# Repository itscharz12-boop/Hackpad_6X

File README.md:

# Hackpad 6x

Hackpad 6x is a small but very over-engineered macropad that I designed because apparently a normal keyboard was not enough :)

The idea was to make a compact control pad that could do a bit of everything: media controls, shortcuts, gaming controls, numpad functions, and displaying useless (but cool) information from my PC.

Basically, I wanted an "infinite keys" macropad where a few buttons could become a lot of buttons through layers.

(yes, this did start as "I'll just make a simple macropad" and then somehow became OLEDs, RGB, and a PC monitoring system. I have no idea how this happened.)

Images of this hackpad can be found in the "images" folder.

Showcase Video (For Hack Club's Stardance event) also available at this link:
https://drive.google.com/file/d/1zJtfslaftjd1Jd6tR7nyllq0msRzVyGn/view?usp=sharing

---

# Features

- 5 different profiles/layers
- Rotary encoder with push button
- OLED display
- RGB lighting
- PC telemetry

The PC telemetry shows:
- CPU usage
- GPU usage
- Volume
- Brightness
(Useful for checking your PC performance without moving your eyes approximately 20cm up to look at your monitor.)

---

# Hardware

The hackpad is built around a Seeed XIAO RP2040.

Parts:

- Seeed XIAO RP2040
- 8x Cherry MX switches
- 8x keycaps
- EC11 rotary encoder
- OLED display
- 16x RGB LEDs
- Custom PCB
- 3D printed case

---

# Assembly

### PCB Assembly

Solder all components onto the PCB:

- Diodes
- RGB LEDs
- OLED
- Rotary encoder
- XIAO RP2040

Please please please check the orientation twice, you won't regret it

### Case Assembly

- Install heat-set inserts
- put the top plate on the bottom 

### Firmware

Hackpad 6x uses QMK firmware.

The firmware includes:

- Layer switching
- Encoder controls
- RGB effects
- OLED graphics
- RAW HID PC communication
  and many more features shown in the video (heres the link again, u should rly watch it: https://drive.google.com/file/d/1zJtfslaftjd1Jd6tR7nyllq0msRzVyGn/view?usp=sharing)

---

### Hackpad DataLink

HackpadDataLink is a Python script that sends PC information to the hackpad.

Currently supported:

- CPU usage
- GPU usage
- Volume
- Brightness

---

# Images

### AI Usage

AI was used minimally throughout this project. The only instance of AI use was fixing compile errors in the firmware. This was done with VS code's built in AI, not quite sure what its called. Aside from this, no other AI tools were used in the making of this project.

Hackpad 6x was built as a personal project to learn PCB design, CAD, QMK firmware, and hardware/software integration. I think this might be the single most electronically complex thing I have ever made.

Huge thanks to Hack Club for making this program possible :)

(Also thanks to Google, Stack Overflow, and whoever wrote the forum post that fixed my kicad)

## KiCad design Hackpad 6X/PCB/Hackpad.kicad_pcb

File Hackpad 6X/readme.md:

# Hackpad 6x

Hackpad 6x is a multi-profile macropad designed to act as an all-purpose desktop control pad. Instead of relying on a large number of physical keys, it uses multiple profiles, a rotary encoder, an OLED display, RGB lighting, and PC telemetry to turn a compact set of inputs into a flexible control surface for media, desktop shortcuts, gaming, and numpad functions.

The goal of this project was to create an “infinite keys” style macropad: a device where a small number of physical inputs can perform a much larger range of tasks through layers.

Hackpad 6x was designed as an omnipurpose desktop macropad rather than a single-purpose keypad. The focus of the project was flexibility: combining multiple profiles, a rotary encoder, OLED feedback, RGB lighting, and PC-side telemetry to make a compact but highly adaptable control device.

---
## Quick Start

1. **Build the hardware** — Assemble the macropad using the PCB, case, switches, and other components listed in the BOM
2. **Flash the firmware** — Install QMK and flash the firmware to the Seeed XIAO RP2040
3. **Install software** — Set up the HackpadDataLink Python script on your PC
4. **Configure profiles** — Customize keybinds and OLED graphics as needed

---

## Features

- Multi-profile layout system for different use cases
- Rotary encoder with push button for quick control input
- OLED display with profile-specific graphics and live system information
- RGB lighting effects with multiple selectable modes
- Media and desktop shortcut controls
- Dual numpad layers for keybinds in games or editors when using 60, 65, 70% keyboards etc.
- Gaming profile for commonly used controls
- PC telemetry support displaying:
  - CPU usage
  - GPU usage
  - System volume
  - Display brightness

---

## Profiles

Hackpad 6x uses 5 profiles:

- Layer 0 — Home / Base
- Layer 1 — Media / Screen Control
- Layer 2 — Numpad A
- Layer 3 — Numpad B
- Layer 4 — Gaming

---

## Hardware

Hackpad 6x is built around a Seeed XIAO RP2040 and includes:

- 8 Cherry MX switches
- 8 keycaps
- 1 rotary encoder with push button
- 1 0.91" OLED display
- 18 RGB LEDs
- 9 diodes
- 6 M3 screws
- 6 M3 heat-set inserts
- Custom 2-layer PCB
- 3D printed case

---

## Bill of Materials (BOM)

| Part                                 | Quantity |
| ------------------------------------ | -------: | 
| Seeed XIAO RP2040                    |        1 | 
| Cherry MX switches                   |        8 |
| Keycaps                              |        8 |
| EC11 rotary encoder with push button |        1 |
| 0.91" OLED display                   |        1 | 
| RGB LEDs                             |       18 |
| Diodes                               |        9 |
| Custom PCB                           |        1 | 
| 3D printed case (BASE + TOP)         |        1 | 
| M3 screws                            |        6 | 
| M3 heatset inserts                   |        6 | 
| Encoder knob                         |        1 | 

---

## Setup & Assembly

### Prerequisites

- QMK firmware toolchain (https://docs.qmk.fm/newbs)
- Python 3.7+ (for HackpadDataLink)
- Git
- Soldering iron and solder

### Assembly Instructions

1. **PCB Assembly**: Solder all components to the PCB according to the manufacturing files
   - Install diodes, rotary encoder, and OLED display
   - Mount the Seeed XIAO RP2040 microcontroller

2. **Switch Installation**: Insert Cherry MX switches into the PCB and secure with keycaps

3. **Case Assembly**: 
   - Install M3 heatset inserts into the 3D printed case pieces
   - Assemble top and bottom case pieces
   - Secure with M3 screws

4. **Testing**: Connect via USB and verify all switches, encoder, and display are working

### Firmware Flashing

1. Clone or download the firmware files from this project
2. Install QMK: `pip install qmk`
3. Set up QMK environment: `qmk setup`
4. Navigate to the firmware directory
5. Flash to the device: `qmk flash -kb hackpad6x -km default`
6. Press the reset button on the XIAO RP2040 when prompted

### Software Setup

1. Install Python dependencies: `pip install -r requirements.txt`
2. Run HackpadDataLink: `python hackpad_datalink.py`
3. The script will automatically detect and connect to the macropad

---

## Firmware

Hackpad 6x uses QMK firmware.

The firmware includes:

- Profile switching
- Encoder modifier behaviour
- RGB mode switching
- OLED profile graphics
- RAW HID support for PC telemetry

If you would like to add/edit any layers, you can edit the firmware and modify the OLED profiles included in the "other" folder, covert them into a bitmap, and add them to the code.

### Configuration Guide

**Customizing Keybinds:**
- Edit the keymap files in the firmware `keymaps` directory
- Modify keycodes for each layer (0-4)
- Refer to QMK documentation for available keycodes
- Re-flash the firmware after making changes

**Customizing OLED Graphics:**
- Design or edit graphics for each profile
- Convert images to bitmap format
- Place bitmap files in the designated folder
- Update the firmware to reference new graphics

**RGB Lighting:**
- Modify RGB animations in the firmware configuration
- Adjust color schemes and animation speeds
- Changes take effect after re-flashing

---

## Hackpad DataLink

A Python script running on the PC sends telemetry values to the macropad over USB, which are then displayed and used by the firmware.

### Telemetry Values

- CPU usage
- GPU usage
- Volume percentage
- Brightness percentage

---

## Production Files

The "production" folder contains the manufacturing and build files needed to physically assemble the project:

- **gerbers.zip** — PCB manufacturing files
- **case.stl** — Exported printable case parts

---

Images can be found in the "Images" folder.

---

## File Structure

hackpad-6x/
├── firmware/              # QMK firmware source code
├── hackpad_datalink/      # Python PC telemetry script
├── production/            # Manufacturing files
│   ├── gerbers.zip        # PCB manufacturing files
│   └── case.stl          # 3D printable case parts
├── other/                 # Additional files
│   ├── OLED_profiles/     # Profile graphics and bitmaps
│   └── reference/        # Documentation and design files
├── images/                # Project photos and diagrams
README.md                 # you are here :)

---

Hackpad 6x was designed and built as a personal project. Special thanks to Hack Club for creating the awesome program behind this!

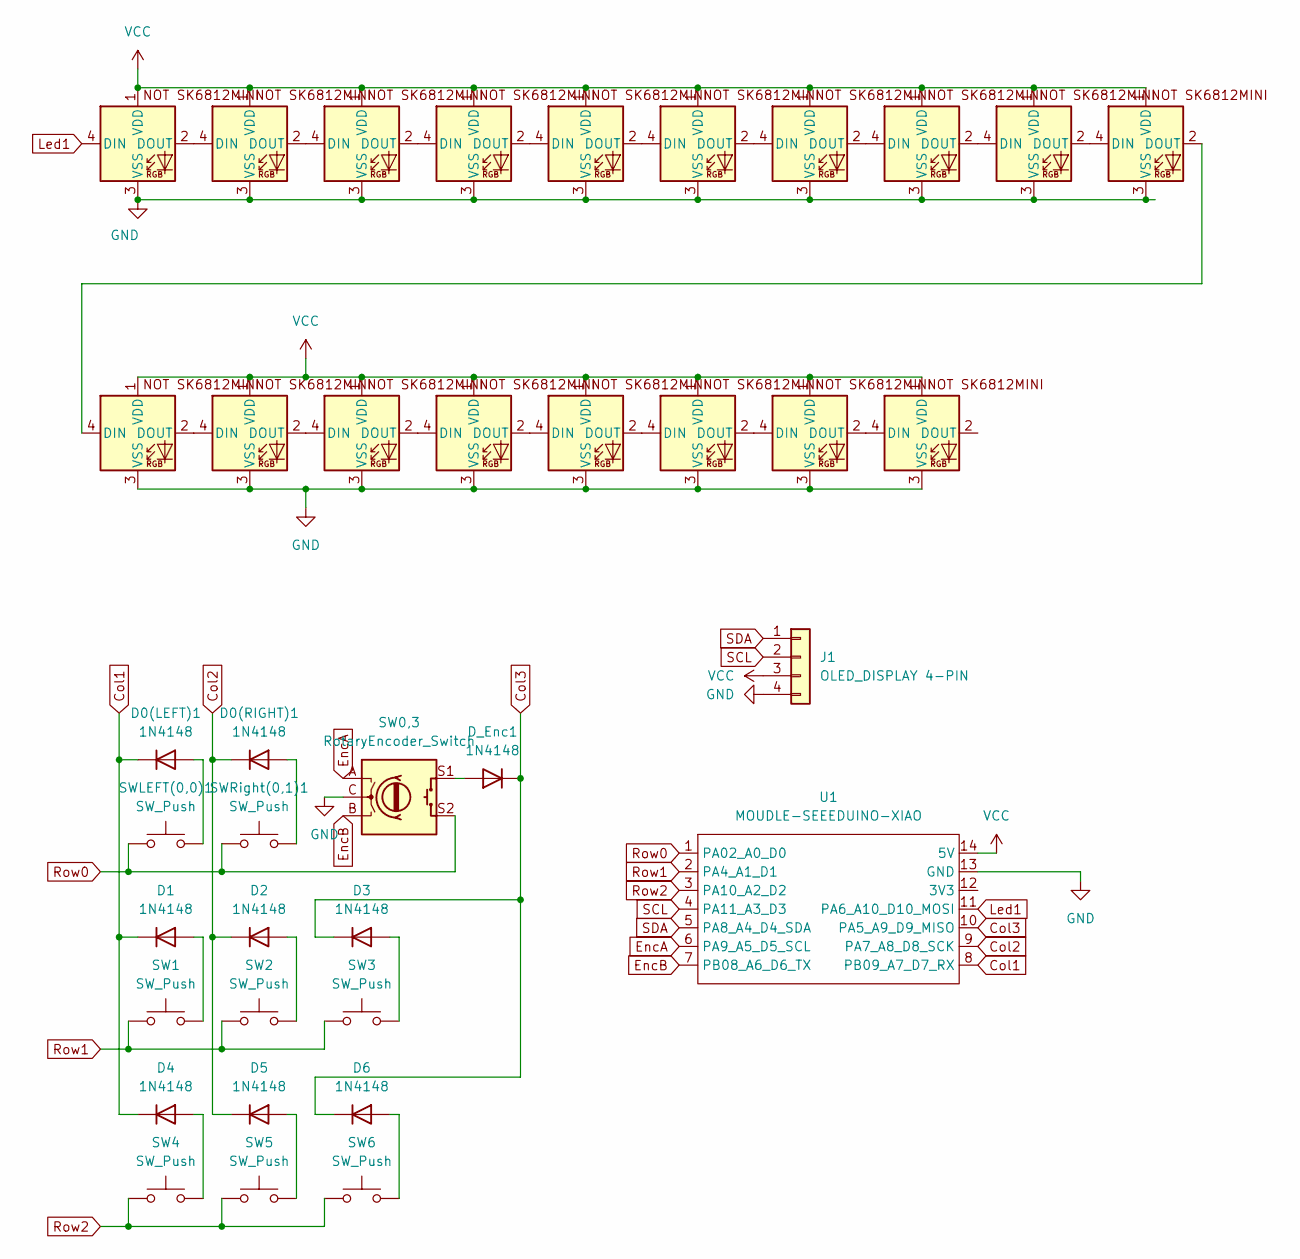
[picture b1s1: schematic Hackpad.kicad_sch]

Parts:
D0(LEFT)1, D0(RIGHT)1, D1, D2, D3, D4, D5, D6: 1N4148; D_DO-35_SOD27_P7.62mm_Horizontal
D15, D16, D17, D18, D19, D20, D21, D22, D24, D25, D26, D27, D28, D29, D30, D31, D32, D33: SK6812MINI-E; SK6812MINI-E_fixed
D_Enc1: 1N4148; D_DO-35_SOD27_P7.62mm_Horizontal
J1: OLED_DISPLAY 4-PIN; PinHeader_1x04_P2.54mm_Vertical
SW0,3: RotaryEncoder_Switch; RotaryEncoder_Alps_EC11E-Switch_Vertical_H20mm
SW1, SW2, SW3, SW4, SW5, SW6: SW_Push; SW_Cherry_MX_1.00u_PCB
SWLEFT(0,0)1: SW_Push; SW_Cherry_MX_1.00u_PCB
SWRight(0,1)1: SW_Push; SW_Cherry_MX_1.00u_PCB
U1: MOUDLE-SEEEDUINO-XIAO; XIAO-Generic-Hybrid-14P-2.54-21X17.8MM

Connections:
Col1: D0(LEFT)1.1 (K), D1.1 (K), D4.1 (K), U1.8 (PB09_A7_D7_RX)
Col2: D0(RIGHT)1.1 (K), D2.1 (K), D5.1 (K), U1.9 (PA7_A8_D8_SCK)
Col3: D3.1 (K), D6.1 (K), D_Enc1.1 (K), U1.10 (PA5_A9_D9_MISO)
EncA: SW0,3.A, U1.6 (PA9_A5_D5_SCL)
EncB: SW0,3.B, U1.7 (PB08_A6_D6_TX)
GND: D15.3 (VSS), D16.3 (VSS), D17.3 (VSS), D18.3 (VSS), D19.3 (VSS), D20.3 (VSS), D21.3 (VSS), D22.3 (VSS), D24.3 (VSS), D25.3 (VSS), D26.3 (VSS), D27.3 (VSS), D28.3 (VSS), D29.3 (VSS), D30.3 (VSS), D31.3 (VSS), D32.3 (VSS), D33.3 (VSS), J1.4, SW0,3.C, U1.13 (GND)
Led1: D15.4 (DIN), U1.11 (PA6_A10_D10_MOSI)
unnamed: D0(LEFT)1.2 (A), SWLEFT(0,0)1.2
unnamed: D0(RIGHT)1.2 (A), SWRight(0,1)1.2
unnamed: D1.2 (A), SW1.2
unnamed: D2.2 (A), SW2.2
unnamed: D3.2 (A), SW3.2
unnamed: D4.2 (A), SW4.2
unnamed: D5.2 (A), SW5.2
unnamed: D6.2 (A), SW6.2
unnamed: D15.2 (DOUT), D16.4 (DIN)
unnamed: D16.2 (DOUT), D17.4 (DIN)
unnamed: D17.2 (DOUT), D18.4 (DIN)
unnamed: D18.2 (DOUT), D24.4 (DIN)
unnamed: D19.4 (DIN), D29.2 (DOUT)
unnamed: D19.2 (DOUT), D20.4 (DIN)
unnamed: D20.2 (DOUT), D21.4 (DIN)
unnamed: D21.2 (DOUT), D22.4 (DIN)
unnamed: D22.2 (DOUT), D30.4 (DIN)
unnamed: D24.2 (DOUT), D25.4 (DIN)
unnamed: D25.2 (DOUT), D26.4 (DIN)
unnamed: D26.2 (DOUT), D27.4 (DIN)
unnamed: D27.2 (DOUT), D28.4 (DIN)
unnamed: D28.2 (DOUT), D29.4 (DIN)
unnamed: D30.2 (DOUT), D31.4 (DIN)
unnamed: D31.2 (DOUT), D32.4 (DIN)
unnamed: D32.2 (DOUT), D33.4 (DIN)
unnamed: D_Enc1.2 (A), SW0,3.S1
Row0: SW0,3.S2, SWLEFT(0,0)1.1, SWRight(0,1)1.1, U1.1 (PA02_A0_D0)
Row1: SW1.1, SW2.1, SW3.1, U1.2 (PA4_A1_D1)
Row2: SW4.1, SW5.1, SW6.1, U1.3 (PA10_A2_D2)
SCL: J1.2, U1.4 (PA11_A3_D3)
SDA: J1.1, U1.5 (PA8_A4_D4_SDA)
VCC: D15.1 (VDD), D16.1 (VDD), D17.1 (VDD), D18.1 (VDD), D19.1 (VDD), D20.1 (VDD), D21.1 (VDD), D22.1 (VDD), D24.1 (VDD), D25.1 (VDD), D26.1 (VDD), D27.1 (VDD), D28.1 (VDD), D29.1 (VDD), D30.1 (VDD), D31.1 (VDD), D32.1 (VDD), D33.1 (VDD), J1.3, U1.14 (5V)

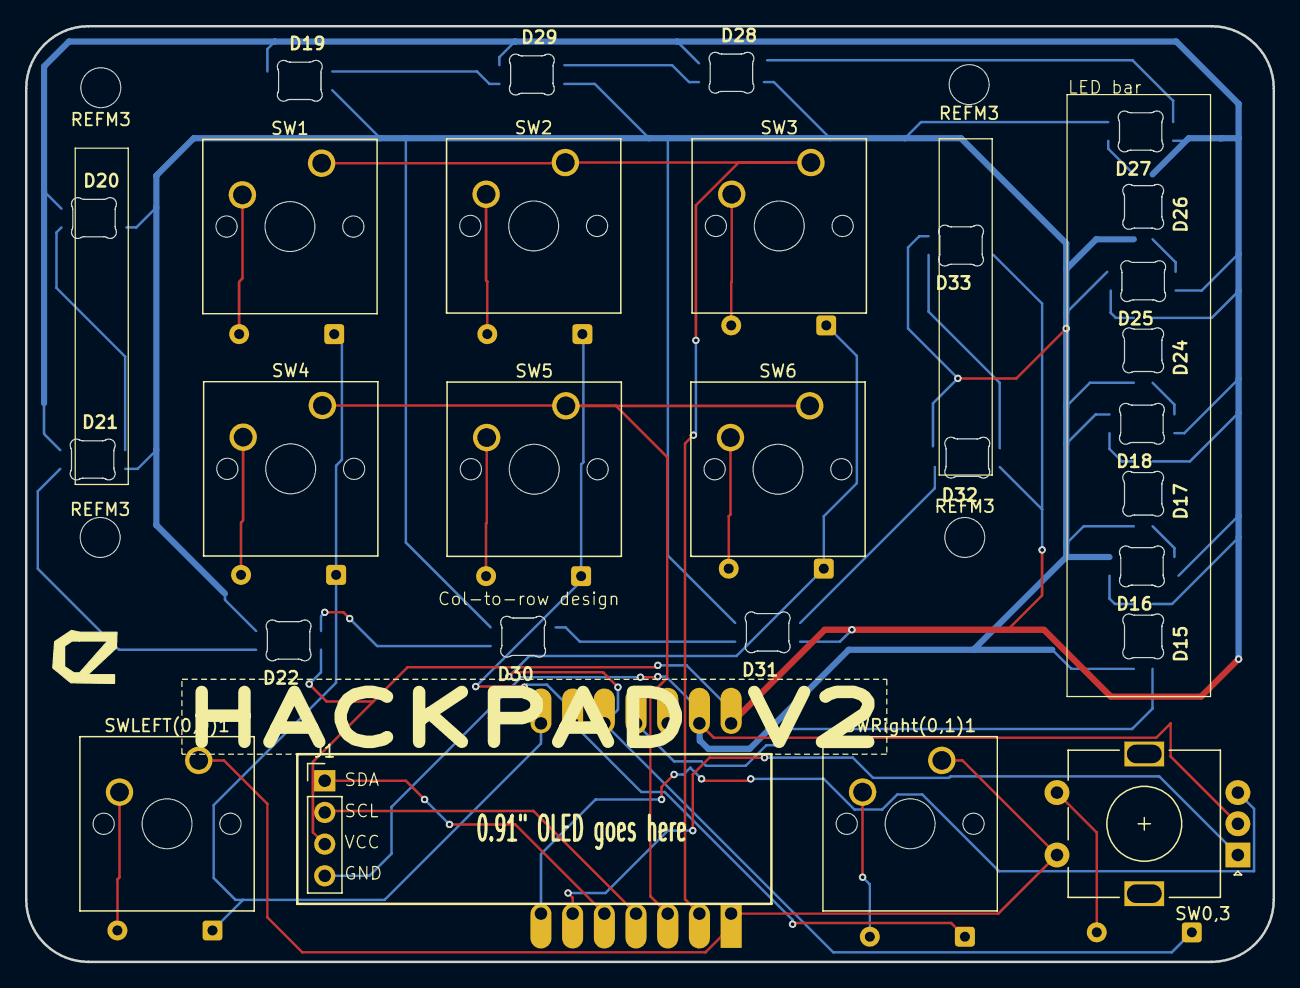
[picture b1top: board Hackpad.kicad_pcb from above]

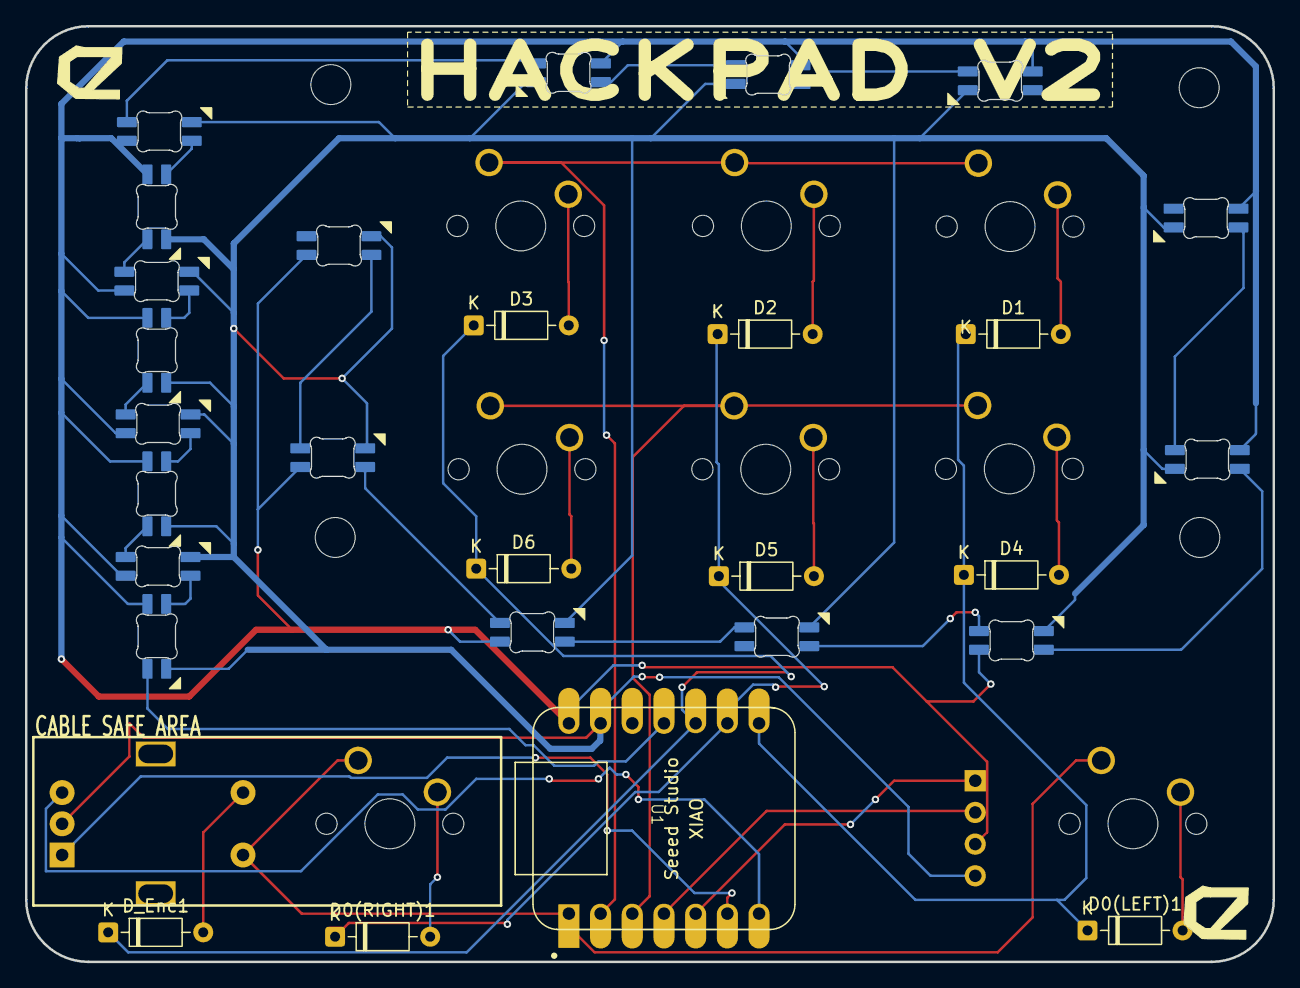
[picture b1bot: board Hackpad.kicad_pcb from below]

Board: 2 copper layers, 100.0 x 75.0 mm, 42 parts (10 on the bottom side), 39 nets.

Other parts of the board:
REFM3, REFM3#2, REFM3#3, REFM3#4: MountingHole_3.2mm_M3
